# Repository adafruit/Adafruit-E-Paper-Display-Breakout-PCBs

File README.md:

# Adafruit-E-Paper-Display-Breakout-PCBs
PCB files for Adafruit E-Paper Display Breakouts

Format is EagleCAD schematic and board layout

For more details, check out the product page at

   * https://www.adafruit.com/product/1028   
   * https://www.adafruit.com/product/3625
   * https://www.adafruit.com/product/4086
   * https://www.adafruit.com/product/4098
   * https://www.adafruit.com/product/4196
   * https://www.adafruit.com/product/4777   
   * https://www.adafruit.com/product/4778
   * https://www.adafruit.com/product/4947

Adafruit invests time and resources providing this open source design, 
please support Adafruit and open-source hardware by purchasing 
products from Adafruit!

Designed by Adafruit Industries.  
Creative Commons Attribution, Share-Alike license, check license.txt for more information
All text above must be included in any redistribution

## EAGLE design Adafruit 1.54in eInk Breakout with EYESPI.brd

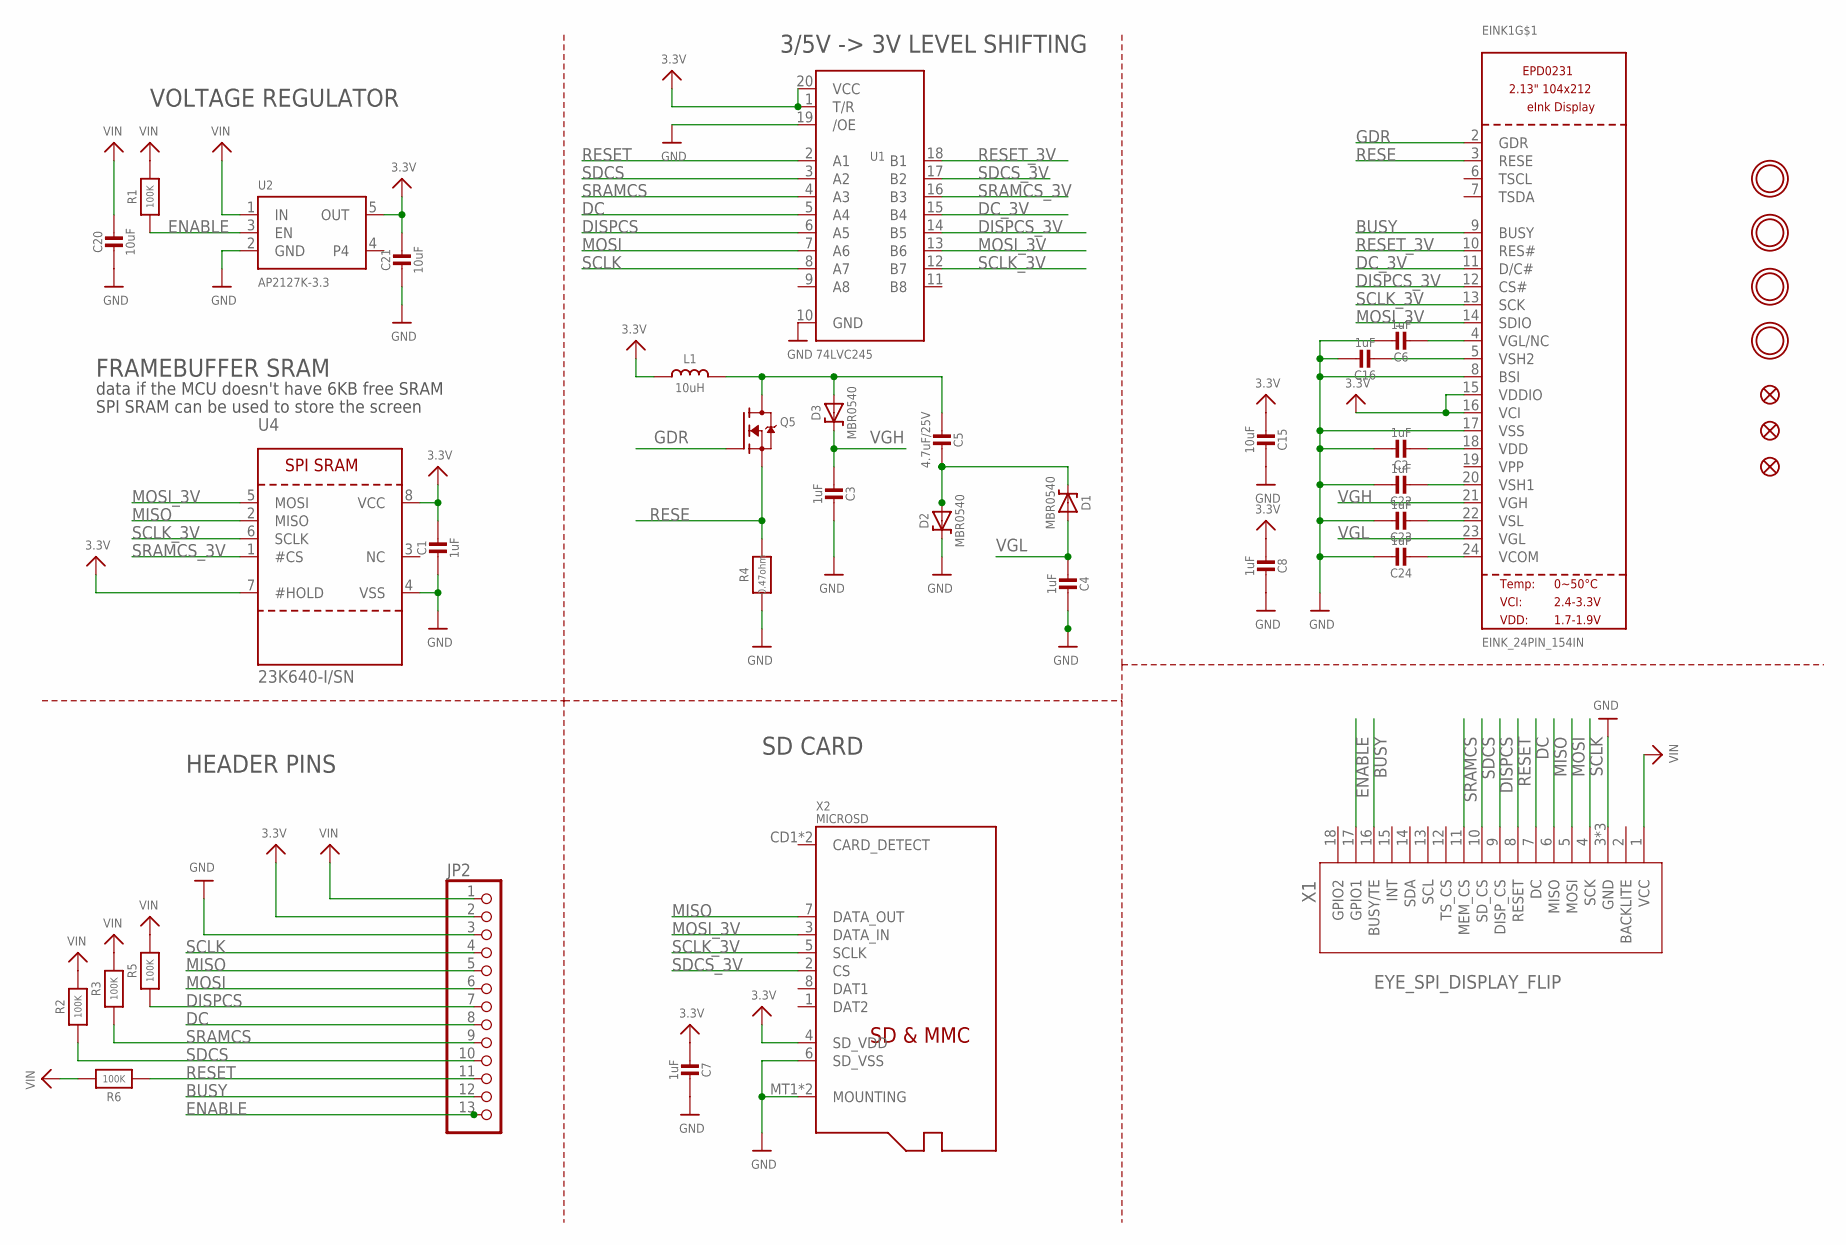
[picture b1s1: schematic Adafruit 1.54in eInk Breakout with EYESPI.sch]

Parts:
C1, C2, C3, C4, C6, C7, C8, C16, C22, C23, C24: 1uF; 0805-NO
C5: 4.7uF/25V; 0805-NO
C15, C20, C21: 10uF; 0805-NO
D1, D2, D3: MBR0540; SOD-123
EINK1: EINK_24PIN_154IN; EINK_154IN
FID1, FID2, FID3: FIDUCIAL_1MM
JP2: HEADER-1X13; 1X13_ROUND_70
L1: 10uH; INDUCTOR_4X4MM_NR401
Q5: IRLML0100; SOT23-3
R1, R2, R3, R5, R6: 100K; 0805-NO
R4: 0.47ohm; 0805_10MGAP
U1: 74LVC245; TSSOP20
U2: AP2127K-3.3; SOT23-5
U4: 23K640-I/SN; SOIC8_150MIL
U$3, U$4, U$5, U$6: MOUNTINGHOLE2.5; MOUNTINGHOLE_2.5_PLATED
X1: EYE_SPI_DISPLAY_FLIP; EYE_SPI_DISPLAY_BOTCONTACT
X2: MICROSD

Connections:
3.3V: C1.1, C7.1, C8.1, C15.2, C21.1, EINK1.15 (VDDIO), EINK1.16 (VCI), JP2.2, L1.P$2 (2), U1.1 (T/R), U1.20 (VCC), U2.5 (OUT), U4.7 (#HOLD), U4.8 (VCC), X2.4 (SD_VDD)
BUSY: EINK1.9 (BUSY), JP2.12, X1.16 (BUSY/TE)
DC: JP2.8, U1.5 (A4), X1.7 (DC)
DC_3V: EINK1.11 (D/C#), U1.15 (B4)
DISPCS: JP2.7, R5.1, U1.6 (A5), X1.9 (DISP_CS)
DISPCS_3V: EINK1.12 (CS#), U1.14 (B5)
ENABLE: JP2.13, R1.1, U2.3 (EN), X1.17 (GPIO1)
GDR: EINK1.2 (GDR), Q5.1 (G)
GND: C1.2, C2.1, C3.2, C4.2, C6.1, C7.2, C8.2, C15.1, C16.1, C20.2, C21.2, C22.1, C23.1, C24.1, D2.C, EINK1.8 (BSI), EINK1.17 (VSS), JP2.3, R4.2, U1.10 (GND), U1.19 (/OE), U2.2 (GND), U4.4 (VSS), X1.3 (GND), X1.SUPPORT1 (GND), X1.SUPPORT2 (GND), X2.6 (SD_VSS), X2.MT1 (MOUNTING), X2.MT2 (MOUNTING)
MISO: JP2.5, U4.2 (MISO), X1.6 (MISO), X2.7 (DATA_OUT)
MOSI: JP2.6, U1.7 (A6), X1.5 (MOSI)
MOSI_3V: EINK1.14 (SDIO), U1.13 (B6), U4.5 (MOSI), X2.3 (DATA_IN)
unnamed: C5.2, D1.C, D2.A
unnamed: C5.1, D3.A, L1.P$1 (1), Q5.3 (D)
unnamed: C16.2, EINK1.5 (VSH2)
unnamed: C2.2, EINK1.18 (VDD)
unnamed: C22.2, EINK1.20 (VSH1)
unnamed: C6.2, EINK1.4 (VGL/NC)
unnamed: C23.2, EINK1.22 (VSL)
unnamed: C24.2, EINK1.24 (VCOM)
RESE: EINK1.3 (RESE), Q5.2 (S), R4.1
RESET: JP2.11, R6.1, U1.2 (A1), X1.8 (RESET)
RESET_3V: EINK1.10 (RES#), U1.18 (B1)
SCLK: JP2.4, U1.8 (A7), X1.4 (SCK)
SCLK_3V: EINK1.13 (SCK), U1.12 (B7), U4.6 (SCLK), X2.5 (SCLK)
SDCS: JP2.10, R2.1, U1.3 (A2), X1.10 (SD_CS)
SDCS_3V: U1.17 (B2), X2.2 (CS)
SRAMCS: JP2.9, R3.1, U1.4 (A3), X1.11 (MEM_CS)
SRAMCS_3V: U1.16 (B3), U4.1 (#CS)
VGH: C3.1, D3.C, EINK1.21 (VGH)
VGL: C4.1, D1.A, EINK1.23 (VGL)
VIN: C20.1, JP2.1, R1.2, R2.2, R3.2, R5.2, R6.2, U2.1 (IN), X1.1 (VCC)

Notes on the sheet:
VOLTAGE REGULATOR
3/5V -> 3V LEVEL SHIFTING
HEADER PINS
FRAMEBUFFER SRAM
SPI SRAM can be used to store the screen
data if the MCU doesn't have 6KB free SRAM
SD CARD

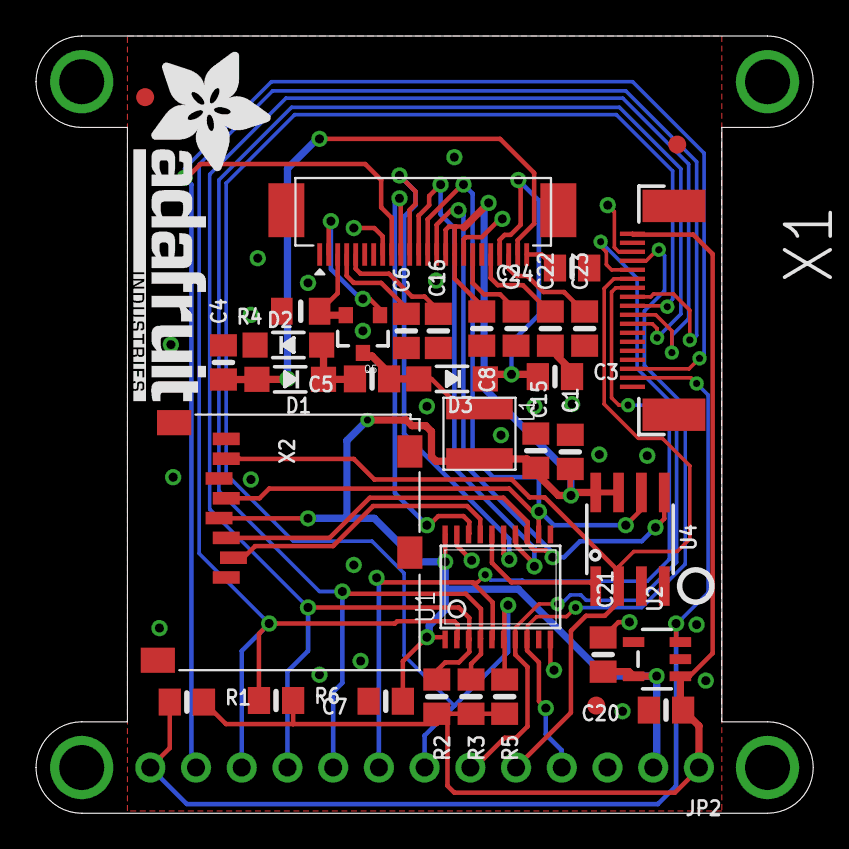
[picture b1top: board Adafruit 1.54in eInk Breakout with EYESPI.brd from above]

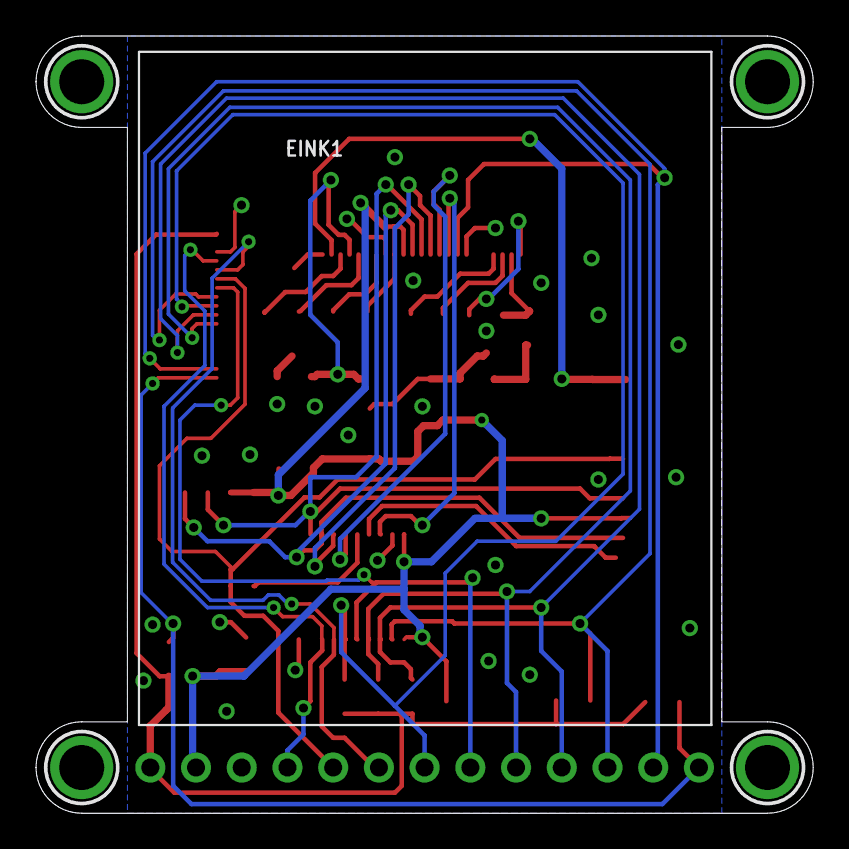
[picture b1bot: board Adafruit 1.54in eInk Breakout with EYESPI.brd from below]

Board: 2 copper layers, 43.2 x 43.2 mm, 70 parts (18 on the bottom side), 32 nets.

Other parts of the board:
PLABEL0: PLABEL0
PLABEL1: PLABEL1
PLABEL2: PLABEL2
PLABEL3: PLABEL3
PLABEL4: PLABEL4
PLABEL5: PLABEL5
PLABEL6: PLABEL6
PLABEL7: PLABEL7
PLABEL8: PLABEL8
PLABEL9: PLABEL9
PLABEL10: PLABEL10
PLABEL11: PLABEL11
PLABEL12: PLABEL12
PLABEL13: PLABEL13
PLABEL14: PLABEL14
PLABEL15: PLABEL15
PLABEL16: PLABEL16
PLABEL17: PLABEL17
PLABEL18: PLABEL18
PLABEL19: PLABEL19
PLABEL20: PLABEL20
PLABEL21: PLABEL21
PLABEL22: PLABEL22
PLABEL23: PLABEL23
PLABEL24: PLABEL24
PLABEL25: PLABEL25
PLABEL26: PLABEL26
PLABEL27: PLABEL27
U$9: PCBFEAT-REV-040
U$28: ADAFRUIT_TEXT_20MM

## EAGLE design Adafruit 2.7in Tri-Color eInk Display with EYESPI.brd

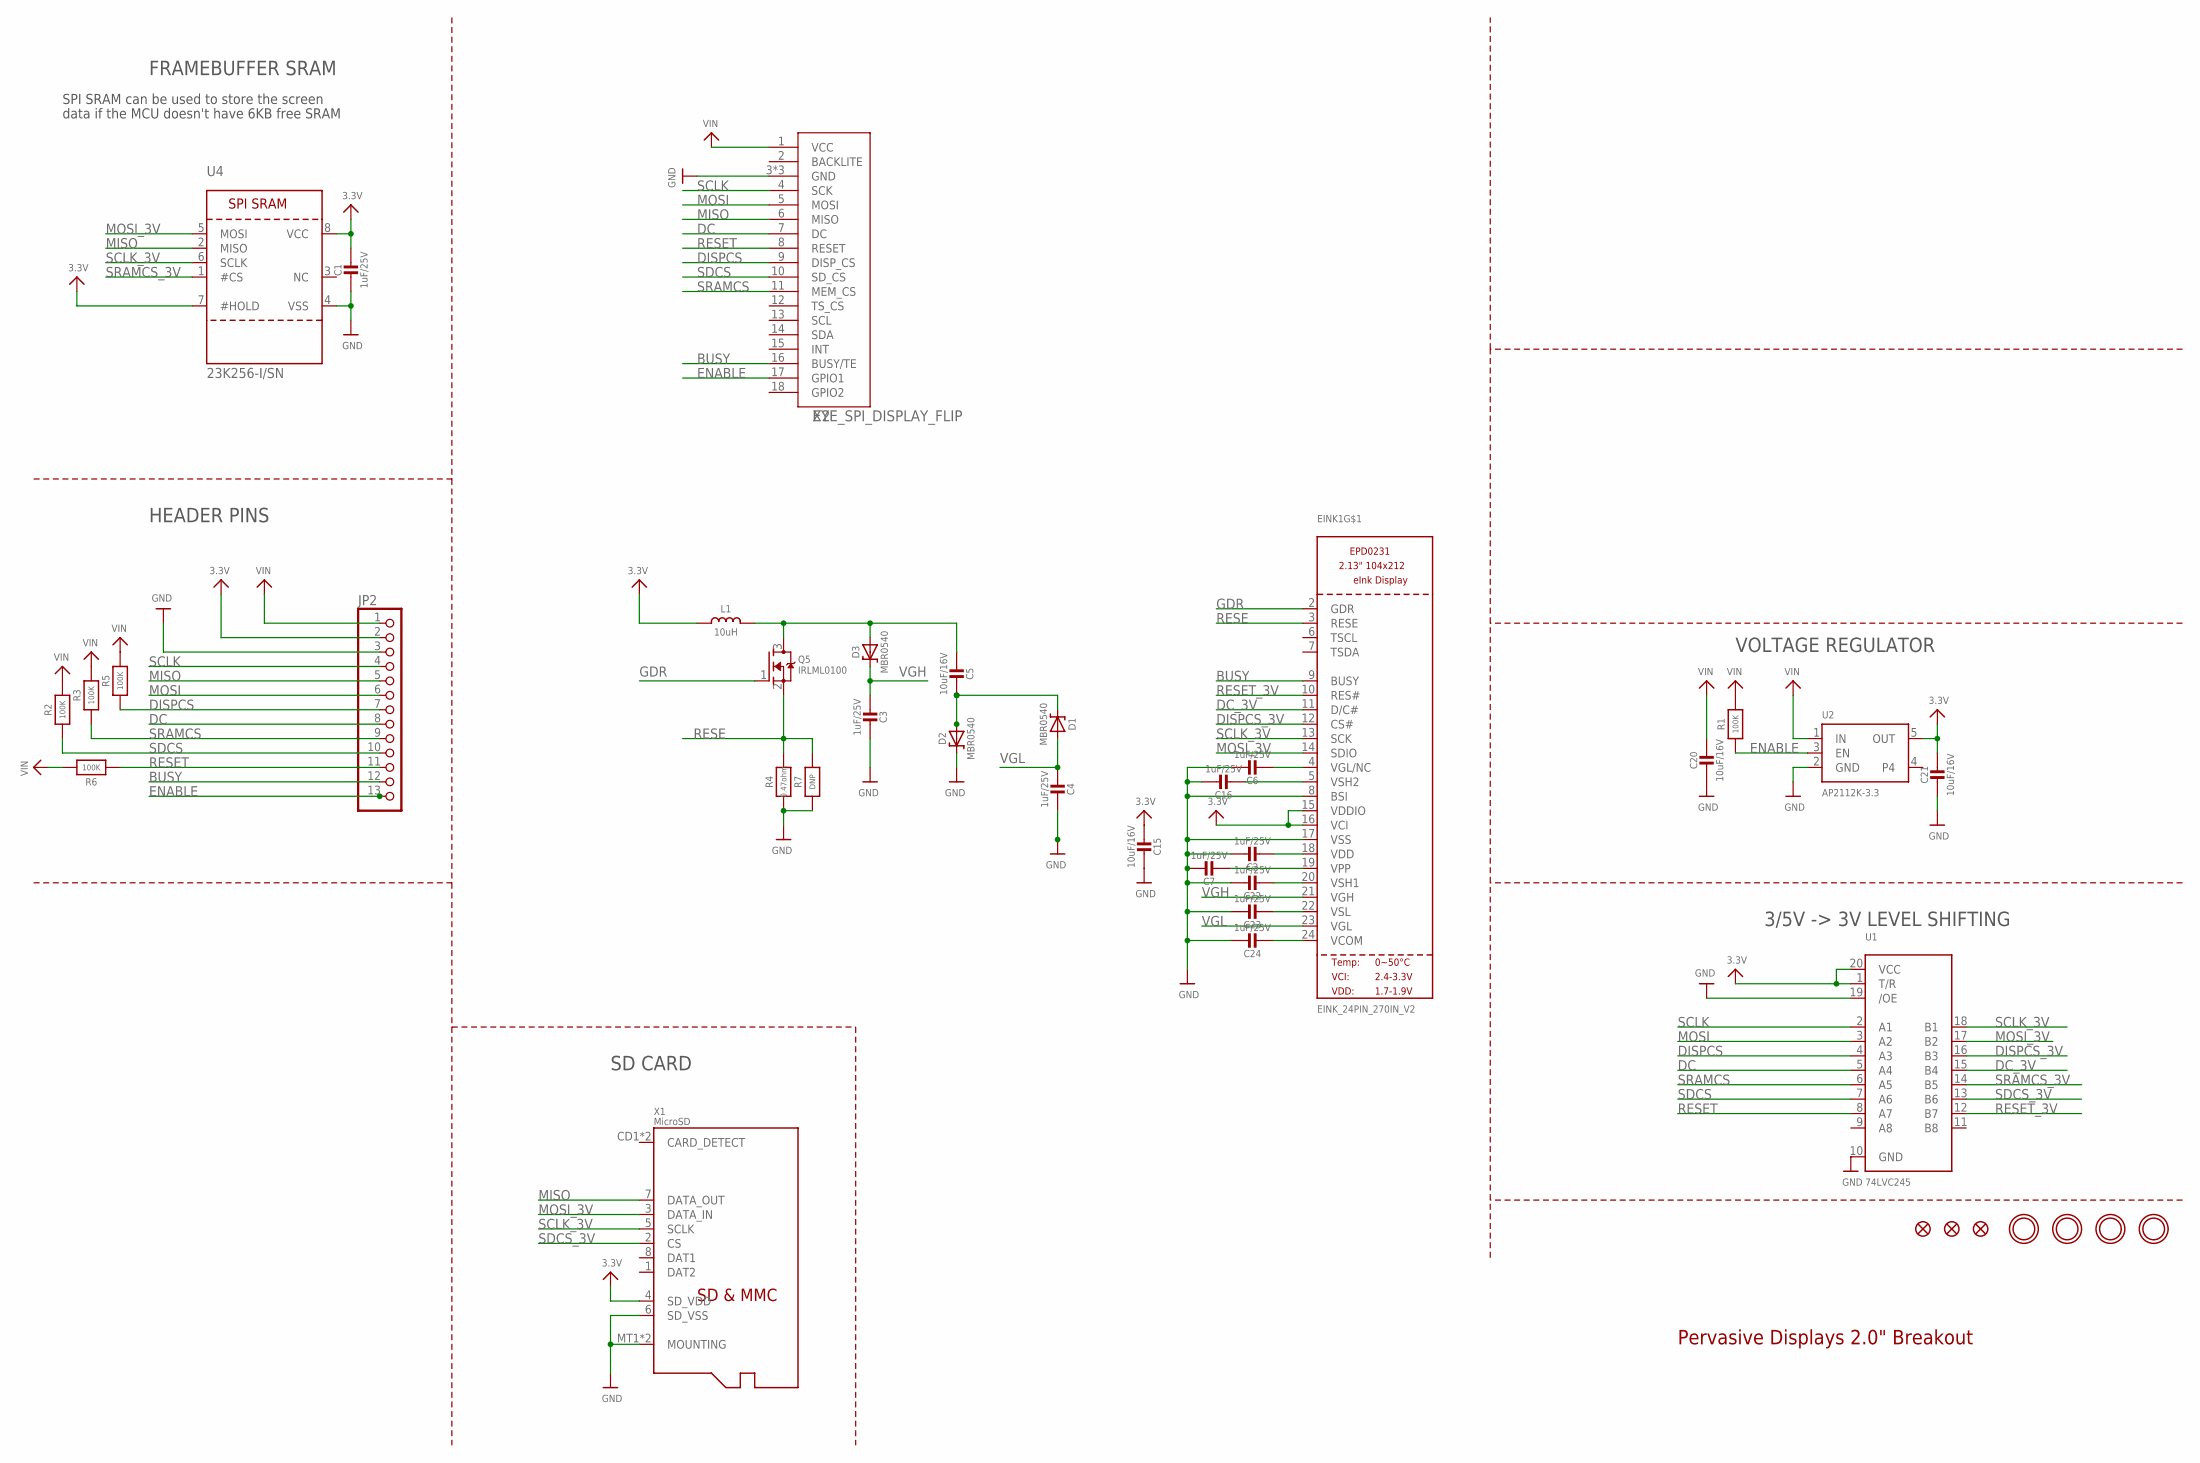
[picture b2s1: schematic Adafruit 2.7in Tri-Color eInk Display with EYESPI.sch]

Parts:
C1, C2, C3, C4, C6, C7, C16, C22, C23, C24: 1uF/25V; 0603-NO
C5, C15, C20, C21: 10uF/16V; 0805-NO
D1, D2, D3: MBR0540; SOD-123
EINK1: EINK_24PIN_270IN_V2; EINK_270IN_V2
FID1, FID2, FID3: FIDUCIAL_1MM
JP2: HEADER-1X13; 1X13_ROUND_70
L1: 10uH; INDUCTOR_4X4MM_NR401
Q5: IRLML0100; SOT23-WIDE
R1, R2, R3, R5, R6: 100K; 0603-NO
R4: 0.47ohm; 0603-NO
R7: DNP; 0603-NO
U1: 74LVC245; TSSOP20
U2: AP2112K-3.3; SOT23-5; JLC_ROTATION 0
U4: 23K256-I/SN; SOIC8_150MIL
U$3, U$4, U$5, U$6: MOUNTINGHOLE2.5; MOUNTINGHOLE_2.5_PLATED
X1: MicroSD; MICROSD
X2: EYE_SPI_DISPLAY_FLIP; EYE_SPI_DISPLAY_BOTCONTACT

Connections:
3.3V: C1.1, C15.2, C21.1, EINK1.15 (VDDIO), EINK1.16 (VCI), JP2.2, L1.P$2 (2), U1.1 (T/R), U1.20 (VCC), U2.5 (OUT), U4.7 (#HOLD), U4.8 (VCC), X1.4 (SD_VDD)
BUSY: EINK1.9 (BUSY), JP2.12, X2.16 (BUSY/TE)
DC: JP2.8, U1.5 (A4), X2.7 (DC)
DC_3V: EINK1.11 (D/C#), U1.15 (B4)
DISPCS: JP2.7, R5.1, U1.4 (A3), X2.9 (DISP_CS)
DISPCS_3V: EINK1.12 (CS#), U1.16 (B3)
ENABLE: JP2.13, R1.1, U2.3 (EN), X2.17 (GPIO1)
GDR: EINK1.2 (GDR), Q5.1 (G)
GND: C1.2, C2.1, C3.2, C4.2, C6.1, C7.1, C15.1, C16.1, C20.2, C21.2, C22.1, C23.1, C24.1, D2.C, EINK1.8 (BSI), EINK1.17 (VSS), JP2.3, R4.2, R7.2, U1.10 (GND), U1.19 (/OE), U2.2 (GND), U4.4 (VSS), X1.6 (SD_VSS), X1.MT1 (MOUNTING), X1.MT2 (MOUNTING), X2.3 (GND), X2.SUPPORT1 (GND), X2.SUPPORT2 (GND)
MISO: JP2.5, U4.2 (MISO), X1.7 (DATA_OUT), X2.6 (MISO)
MOSI: JP2.6, U1.3 (A2), X2.5 (MOSI)
MOSI_3V: EINK1.14 (SDIO), U1.17 (B2), U4.5 (MOSI), X1.3 (DATA_IN)
unnamed: C7.2, EINK1.19 (VPP)
unnamed: C5.2, D1.C, D2.A
unnamed: C5.1, D3.A, L1.P$1 (1), Q5.3 (D)
unnamed: C16.2, EINK1.5 (VSH2)
unnamed: C2.2, EINK1.18 (VDD)
unnamed: C22.2, EINK1.20 (VSH1)
unnamed: C6.2, EINK1.4 (VGL/NC)
unnamed: C23.2, EINK1.22 (VSL)
unnamed: C24.2, EINK1.24 (VCOM)
RESE: EINK1.3 (RESE), Q5.2 (S), R4.1, R7.1
RESET: JP2.11, R6.1, U1.8 (A7), X2.8 (RESET)
RESET_3V: EINK1.10 (RES#), U1.12 (B7)
SCLK: JP2.4, U1.2 (A1), X2.4 (SCK)
SCLK_3V: EINK1.13 (SCK), U1.18 (B1), U4.6 (SCLK), X1.5 (SCLK)
SDCS: JP2.10, R2.1, U1.7 (A6), X2.10 (SD_CS)
SDCS_3V: U1.13 (B6), X1.2 (CS)
SRAMCS: JP2.9, R3.1, U1.6 (A5), X2.11 (MEM_CS)
SRAMCS_3V: U1.14 (B5), U4.1 (#CS)
VGH: C3.1, D3.C, EINK1.21 (VGH)
VGL: C4.1, D1.A, EINK1.23 (VGL)
VIN: C20.1, JP2.1, R1.2, R2.2, R3.2, R5.2, R6.2, U2.1 (IN), X2.1 (VCC)

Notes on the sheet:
Pervasive Displays 2.0" Breakout
VOLTAGE REGULATOR
3/5V -> 3V LEVEL SHIFTING
HEADER PINS
FRAMEBUFFER SRAM
SPI SRAM can be used to store the screen
data if the MCU doesn't have 6KB free SRAM
SD CARD

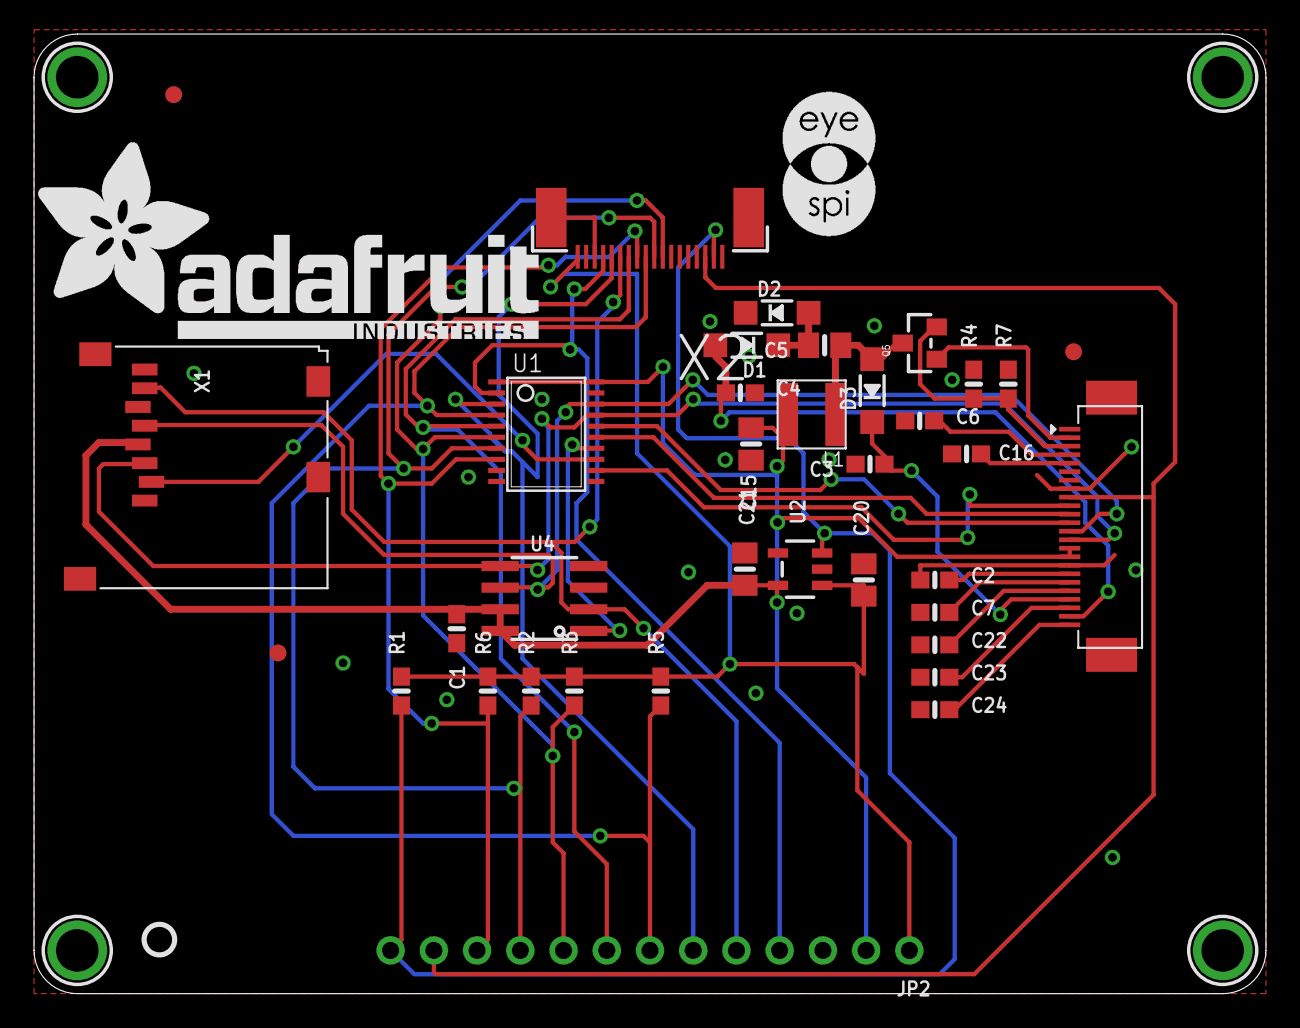
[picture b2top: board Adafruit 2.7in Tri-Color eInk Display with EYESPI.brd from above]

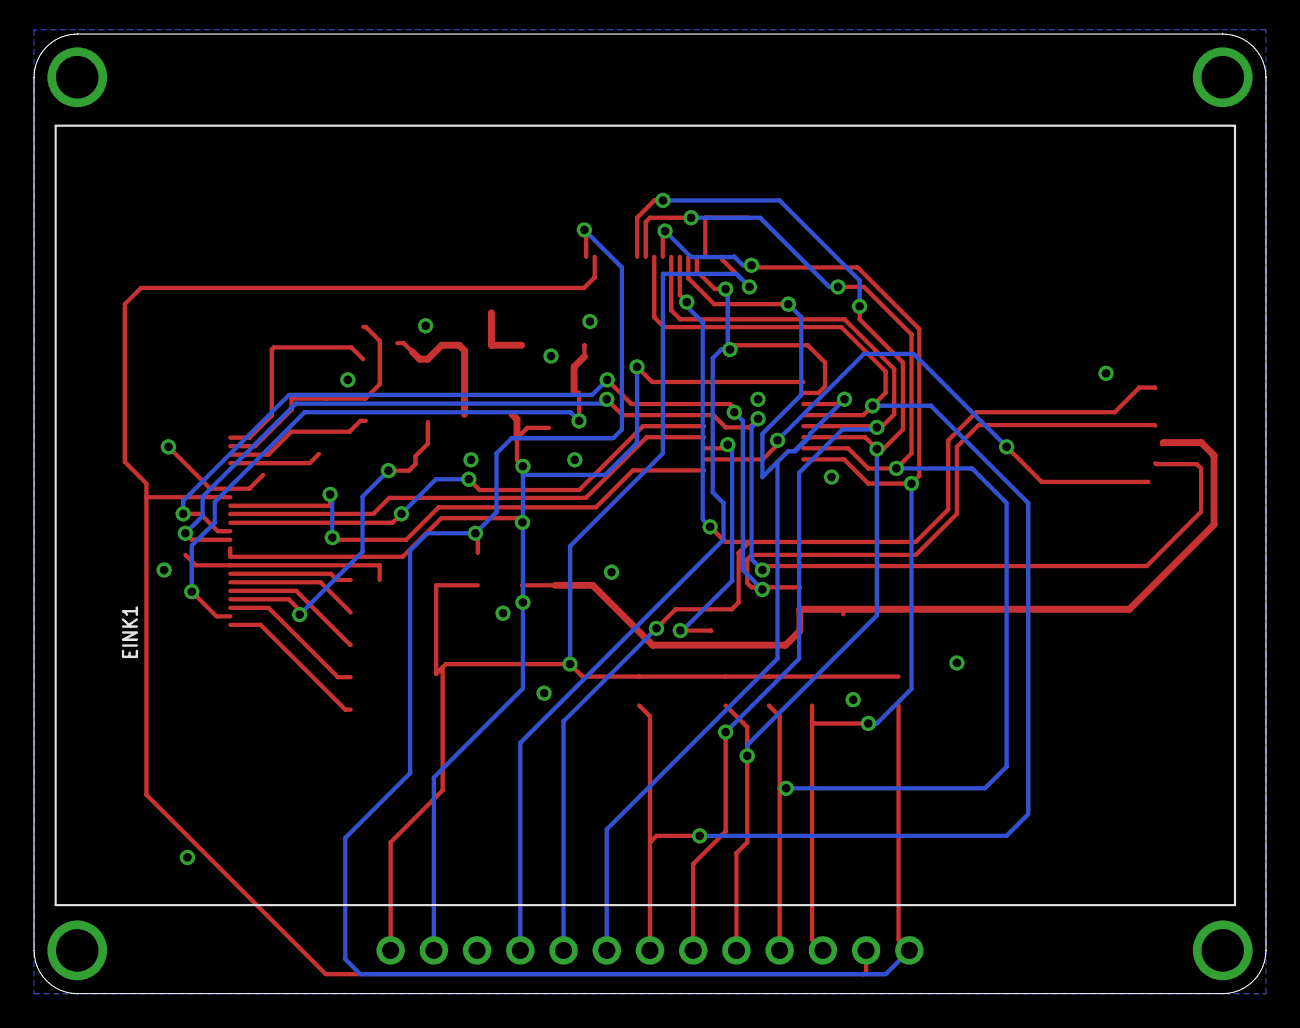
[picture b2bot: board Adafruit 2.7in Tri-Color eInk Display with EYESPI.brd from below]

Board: 2 copper layers, 72.4 x 56.4 mm, 72 parts (15 on the bottom side), 33 nets.

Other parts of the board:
PLABEL0: PLABEL0
PLABEL1: PLABEL1
PLABEL2: PLABEL2
PLABEL3: PLABEL3
PLABEL4: PLABEL4
PLABEL5: PLABEL5
PLABEL6: PLABEL6
PLABEL7: PLABEL7
PLABEL8: PLABEL8
PLABEL9: PLABEL9
PLABEL10: PLABEL10
PLABEL11: PLABEL11
PLABEL12: PLABEL12
PLABEL13: PLABEL13
PLABEL14: PLABEL14
PLABEL15: PLABEL15
PLABEL16: PLABEL16
PLABEL17: PLABEL17
PLABEL18: PLABEL18
PLABEL19: PLABEL19
PLABEL20: PLABEL20
PLABEL21: PLABEL21
PLABEL22: PLABEL22
PLABEL23: PLABEL23
PLABEL24: PLABEL24
PLABEL25: PLABEL25
PLABEL26: PLABEL26
PLABEL27: PLABEL27
PLABEL28: PLABEL28
U$1: EYESPI_MINI_LOGO
U$9: PCBFEAT-REV-040
U$39: ADAFRUIT_TEXT_30MM

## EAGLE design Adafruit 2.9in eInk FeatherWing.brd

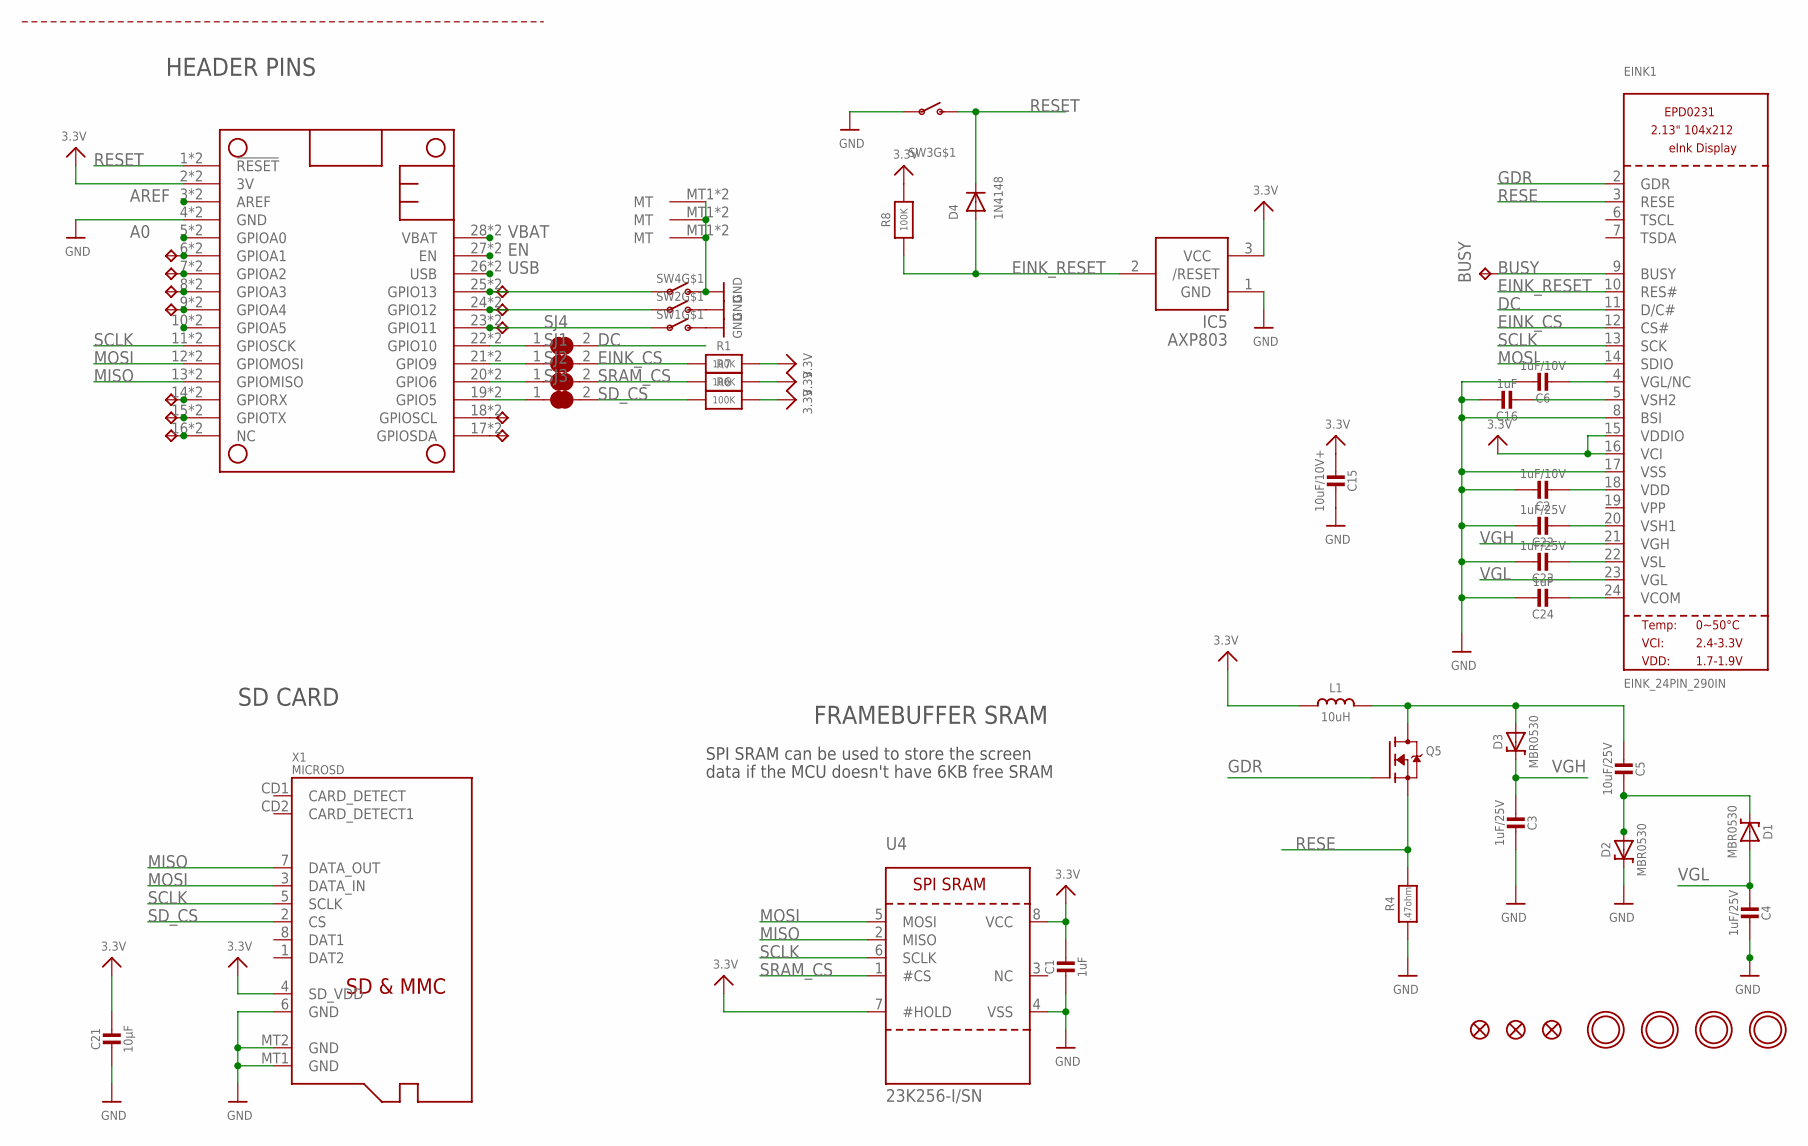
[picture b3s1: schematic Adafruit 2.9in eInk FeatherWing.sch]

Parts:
BUSY: TPTP15SQ; TP15SQ
C1: 1uF; 0805_10MGAP
C2, C6: 1uF/10V; 0805-NO
C3, C4, C22, C23: 1uF/25V; 0805-NO
C5: 10uF/25V; 0805-NO
C15: 10uF/10V+; 0805-NO
C16, C24: 1uF; 0805-NO
C21: 10µF; 0805-NO
D1, D2, D3: MBR0530; SOD-123
D4: 1N4148; SOD-323F
EINK1: EINK_24PIN_290IN; EINK_290IN
FID1, FID2, FID3: FIDUCIAL_1MM
IC5: AXP803; SOT23
L1: 10uH; INDUCTOR_4X4MM_NR401
MS1: FEATHERWING_SMTDUALNOHOLES; FEATHERWING_SMT_NOHOLES
Q5: IRLML0100; SOT23-3
R1, R6, R7, R8: 100K; 0603-NO
R4: .47ohm; 0805_10MGAP
SJ1, SJ2, SJ3, SJ4: SOLDERJUMPER_CLOSED; SOLDERJUMPER_CLOSEDWIRE
SW1, SW2, SW3, SW4: SWITCH_SPST_TACT_RA; SPST_TACTILE_RA
TP1, TP2, TP3, TP4, TP5, TP6, TP7, TP8, TP9, TP11, TP12, TP13: TPTP15SQ; TP15SQ
U4: 23K256-I/SN; SOIC8_150MIL
U$3, U$4, U$5, U$6: MOUNTINGHOLE2.5; MOUNTINGHOLE_2.5_PLATED
X1: MICROSD

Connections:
3.3V: C1.1, C15.2, C21.1, EINK1.15 (VDDIO), EINK1.16 (VCI), IC5.3 (VCC), L1.P$2 (2), MS1.2 (3V), MS1.2B (3V), R1.2, R6.2, R7.2, R8.2, U4.7 (#HOLD), U4.8 (VCC), X1.4 (SD_VDD)
A0: MS1.5 (GPIOA0), MS1.5B (GPIOA0)
AREF: MS1.3 (AREF), MS1.3B (AREF)
BUSY: BUSY.TP, EINK1.9 (BUSY)
DC: EINK1.11 (D/C#), SJ4.2
EINK_CS: EINK1.12 (CS#), R1.1, SJ1.2
EINK_RESET: D4.A, EINK1.10 (RES#), IC5.2 (/RESET), R8.1
EN: MS1.27 (EN), MS1.27B (EN)
GDR: EINK1.2 (GDR), Q5.1 (G)
GND: C1.2, C2.1, C3.2, C4.2, C6.1, C15.1, C16.1, C21.2, C22.1, C23.1, C24.1, D2.C, EINK1.8 (BSI), EINK1.17 (VSS), IC5.1 (GND), MS1.4 (GND), MS1.4B (GND), R4.2, SW1.2 (S), SW1.MT1 (MT), SW1.MT2 (MT), SW2.2 (S), SW2.MT1 (MT), SW2.MT2 (MT), SW3.1, SW4.2 (S), SW4.MT1 (MT), SW4.MT2 (MT), U4.4 (VSS), X1.6 (GND), X1.MT1 (GND), X1.MT2 (GND)
H: MS1.19 (GPIO5), MS1.19B (GPIO5), SJ3.1
I: MS1.20 (GPIO6), MS1.20B (GPIO6), SJ2.1
J: MS1.21 (GPIO9), MS1.21B (GPIO9), SJ1.1
K: MS1.22 (GPIO10), MS1.22B (GPIO10), SJ4.1
MISO: MS1.13 (GPIOMISO), MS1.13B (GPIOMISO), U4.2 (MISO), X1.7 (DATA_OUT)
MOSI: EINK1.14 (SDIO), MS1.12 (GPIOMOSI), MS1.12B (GPIOMOSI), U4.5 (MOSI), X1.3 (DATA_IN)
unnamed: MS1.10 (GPIOA5), MS1.10B (GPIOA5)
unnamed: C5.2, D1.C, D2.A
unnamed: C5.1, D3.A, L1.P$1 (1), Q5.3 (D)
unnamed: C16.2, EINK1.5 (VSH2)
unnamed: C2.2, EINK1.18 (VDD)
unnamed: C22.2, EINK1.20 (VSH1)
unnamed: MS1.6 (GPIOA1), MS1.6B (GPIOA1), TP6.TP
unnamed: C6.2, EINK1.4 (VGL/NC)
unnamed: MS1.7 (GPIOA2), MS1.7B (GPIOA2), TP7.TP
unnamed: MS1.8 (GPIOA3), MS1.8B (GPIOA3), TP8.TP
unnamed: MS1.9 (GPIOA4), MS1.9B (GPIOA4), TP9.TP
unnamed: MS1.14 (GPIORX), MS1.14B (GPIORX), TP11.TP
unnamed: MS1.15 (GPIOTX), MS1.15B (GPIOTX), TP12.TP
unnamed: MS1.16 (NC), MS1.16B (NC), TP13.TP
unnamed: MS1.17 (GPIOSDA), MS1.17B (GPIOSDA), TP4.TP
unnamed: MS1.18 (GPIOSCL), MS1.18B (GPIOSCL), TP3.TP
unnamed: MS1.23 (GPIO11), MS1.23B (GPIO11), SW1.1, TP1.TP
unnamed: MS1.24 (GPIO12), MS1.24B (GPIO12), SW2.1, TP2.TP
unnamed: MS1.25 (GPIO13), MS1.25B (GPIO13), SW4.1, TP5.TP
unnamed: C23.2, EINK1.22 (VSL)
unnamed: C24.2, EINK1.24 (VCOM)
RESE: EINK1.3 (RESE), Q5.2 (S), R4.1
RESET: D4.C, MS1.1 (!RESET), MS1.1B (!RESET), SW3.2 (S)
SCLK: EINK1.13 (SCK), MS1.11 (GPIOSCK), MS1.11B (GPIOSCK), U4.6 (SCLK), X1.5 (SCLK)
SD_CS: R6.1, SJ3.2, X1.2 (CS)
SRAM_CS: R7.1, SJ2.2, U4.1 (#CS)
USB: MS1.26 (USB), MS1.26B (USB)
VBAT: MS1.28 (VBAT), MS1.28B (VBAT)
VGH: C3.1, D3.C, EINK1.21 (VGH)
VGL: C4.1, D1.A, EINK1.23 (VGL)

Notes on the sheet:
HEADER PINS
FRAMEBUFFER SRAM
SPI SRAM can be used to store the screen
data if the MCU doesn't have 6KB free SRAM
SD CARD

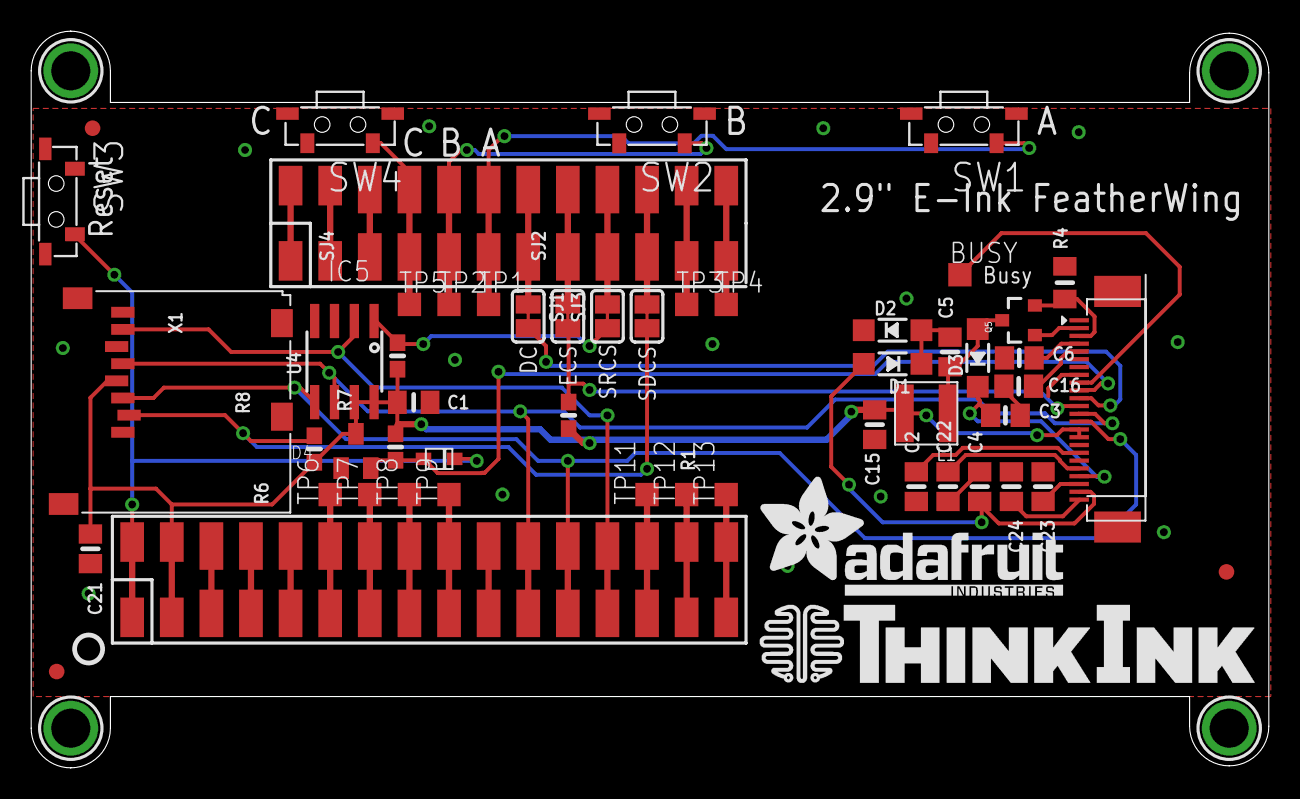
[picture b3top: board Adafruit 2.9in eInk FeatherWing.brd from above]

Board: 2 copper layers, 79.4 x 47.2 mm, 59 parts (1 on the bottom side), 46 nets.

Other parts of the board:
U$8: THINKINK_1.25IN
U$9: PCBFEAT-REV-040
U$17: ADAFRUIT_TEXT_20MM

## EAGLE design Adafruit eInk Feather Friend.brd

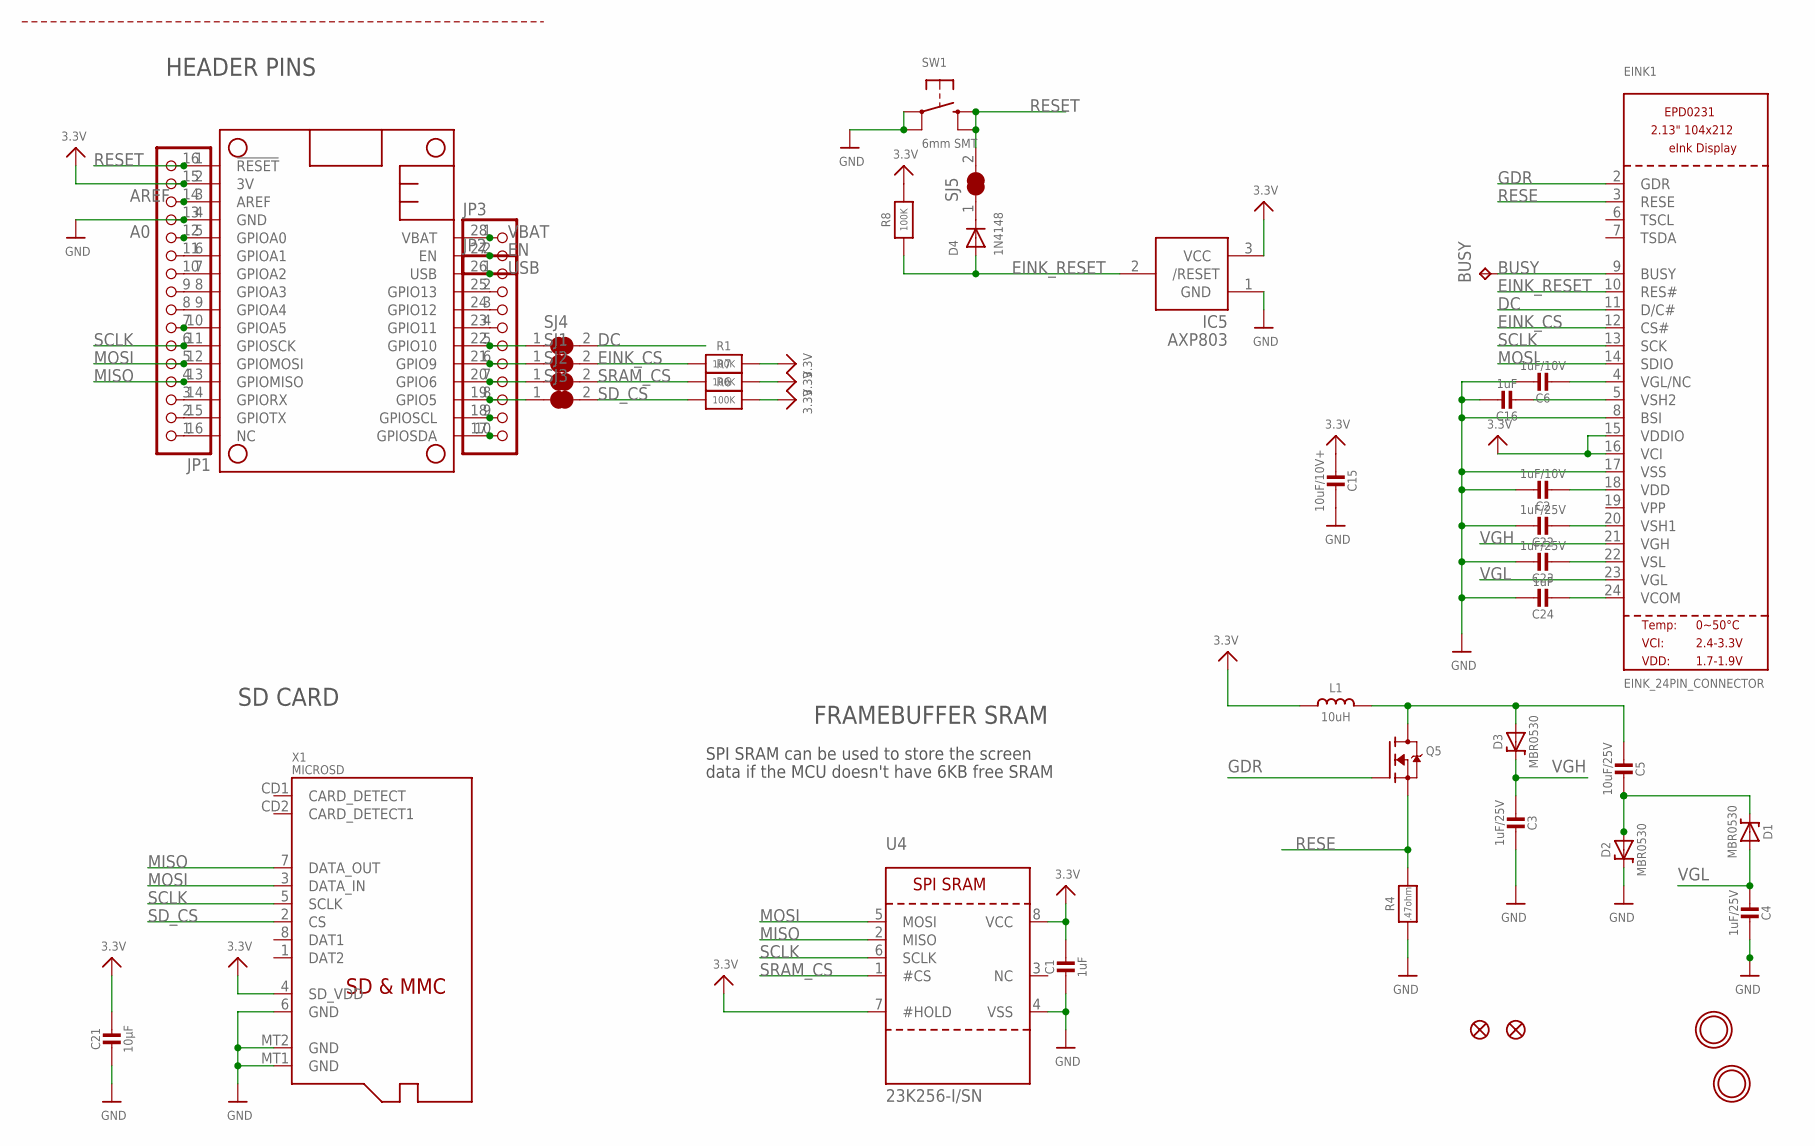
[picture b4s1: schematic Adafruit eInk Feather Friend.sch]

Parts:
BUSY: TPTP15SQ; TP15SQ
C1: 1uF; 0805_10MGAP
C2, C6: 1uF/10V; 0805-NO
C3, C4, C22, C23: 1uF/25V; 0805-NO
C5: 10uF/25V; 0805-NO
C15: 10uF/10V+; 0805-NO
C16, C24: 1uF; 0805-NO
C21: 10µF; 0805-NO
D1, D2, D3: MBR0530; SOD-123
D4: 1N4148; SOD-323F
EINK1: EINK_24PIN_CONNECTOR; EINK_24PIN
FID1, FID3: FIDUCIAL_1MM
IC5: AXP803; SOT23
JP1: HEADER-1X16ROUND; 1X16_ROUND
JP2: HEADER-1X10ROUND; 1X10_ROUND
JP3: HEADER-1X2ROUND; 1X02_ROUND
L1: 10uH; INDUCTOR_4X4MM_NR401
MS1: FEATHERWING_NOHOLES
Q5: IRLML0100; SOT23-3
R1, R6, R7, R8: 100K; 0603-NO
R4: .47ohm; 0805_10MGAP
SJ1, SJ2, SJ3, SJ4, SJ5: SOLDERJUMPER_CLOSED; SOLDERJUMPER_CLOSEDWIRE
SW1: 6mm SMT; BTN_KMR2_4.6X2.8
U4: 23K256-I/SN; SOIC8_150MIL
U$3, U$4: MOUNTINGHOLE2.5; MOUNTINGHOLE_2.5_PLATED
X1: MICROSD

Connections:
3.3V: C1.1, C15.2, C21.1, EINK1.15 (VDDIO), EINK1.16 (VCI), IC5.3 (VCC), JP1.15, L1.P$2 (2), MS1.2 (3V), R1.2, R6.2, R7.2, R8.2, U4.7 (#HOLD), U4.8 (VCC), X1.4 (SD_VDD)
A0: JP1.12, MS1.5 (GPIOA0)
AREF: JP1.14, MS1.3 (AREF)
BUSY: BUSY.TP, EINK1.9 (BUSY)
DC: EINK1.11 (D/C#), SJ4.2
EINK_CS: EINK1.12 (CS#), R1.1, SJ1.2
EINK_RESET: D4.A, EINK1.10 (RES#), IC5.2 (/RESET), R8.1
EN: JP3.2, MS1.27 (EN)
GDR: EINK1.2 (GDR), Q5.1 (G)
GND: C1.2, C2.1, C3.2, C4.2, C6.1, C15.1, C16.1, C21.2, C22.1, C23.1, C24.1, D2.C, EINK1.8 (BSI), EINK1.17 (VSS), IC5.1 (GND), JP1.13, MS1.4 (GND), R4.2, SW1.A, SW1.A' (P1), U4.4 (VSS), X1.6 (GND), X1.MT1 (GND), X1.MT2 (GND)
H: JP2.8, MS1.19 (GPIO5), SJ3.1
I: JP2.7, MS1.20 (GPIO6), SJ2.1
J: JP2.6, MS1.21 (GPIO9), SJ1.1
K: JP2.5, MS1.22 (GPIO10), SJ4.1
MISO: JP1.4, MS1.13 (GPIOMISO), U4.2 (MISO), X1.7 (DATA_OUT)
MOSI: EINK1.14 (SDIO), JP1.5, MS1.12 (GPIOMOSI), U4.5 (MOSI), X1.3 (DATA_IN)
unnamed: JP1.7, MS1.10 (GPIOA5)
unnamed: C5.2, D1.C, D2.A
unnamed: C5.1, D3.A, L1.P$1 (1), Q5.3 (D)
unnamed: C16.2, EINK1.5 (VSH2)
unnamed: C2.2, EINK1.18 (VDD)
unnamed: C22.2, EINK1.20 (VSH1)
unnamed: D4.C, SJ5.1
unnamed: JP1.11, MS1.6 (GPIOA1)
unnamed: C6.2, EINK1.4 (VGL/NC)
unnamed: JP1.10, MS1.7 (GPIOA2)
unnamed: JP1.9, MS1.8 (GPIOA3)
unnamed: JP1.8, MS1.9 (GPIOA4)
unnamed: JP1.3, MS1.14 (GPIORX)
unnamed: JP1.2, MS1.15 (GPIOTX)
unnamed: JP1.1, MS1.16 (NC)
unnamed: JP2.10, MS1.17 (GPIOSDA)
unnamed: JP2.9, MS1.18 (GPIOSCL)
unnamed: JP2.4, MS1.23 (GPIO11)
unnamed: JP2.3, MS1.24 (GPIO12)
unnamed: JP2.2, MS1.25 (GPIO13)
unnamed: C23.2, EINK1.22 (VSL)
unnamed: C24.2, EINK1.24 (VCOM)
RESE: EINK1.3 (RESE), Q5.2 (S), R4.1
RESET: JP1.16, MS1.1 (!RESET), SJ5.2, SW1.B (S), SW1.B' (S1)
SCLK: EINK1.13 (SCK), JP1.6, MS1.11 (GPIOSCK), U4.6 (SCLK), X1.5 (SCLK)
SD_CS: R6.1, SJ3.2, X1.2 (CS)
SRAM_CS: R7.1, SJ2.2, U4.1 (#CS)
USB: JP2.1, MS1.26 (USB)
VBAT: JP3.1, MS1.28 (VBAT)
VGH: C3.1, D3.C, EINK1.21 (VGH)
VGL: C4.1, D1.A, EINK1.23 (VGL)

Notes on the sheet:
HEADER PINS
FRAMEBUFFER SRAM
SPI SRAM can be used to store the screen
data if the MCU doesn't have 6KB free SRAM
SD CARD

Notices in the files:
parts and their libraries:
microbuilder: This work is placed in the public domain, and may be freely used for commercial and non-commercial work with the following conditions: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
